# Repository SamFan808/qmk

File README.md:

# qmk
QMK related mechanical keyboard firmware and layouts

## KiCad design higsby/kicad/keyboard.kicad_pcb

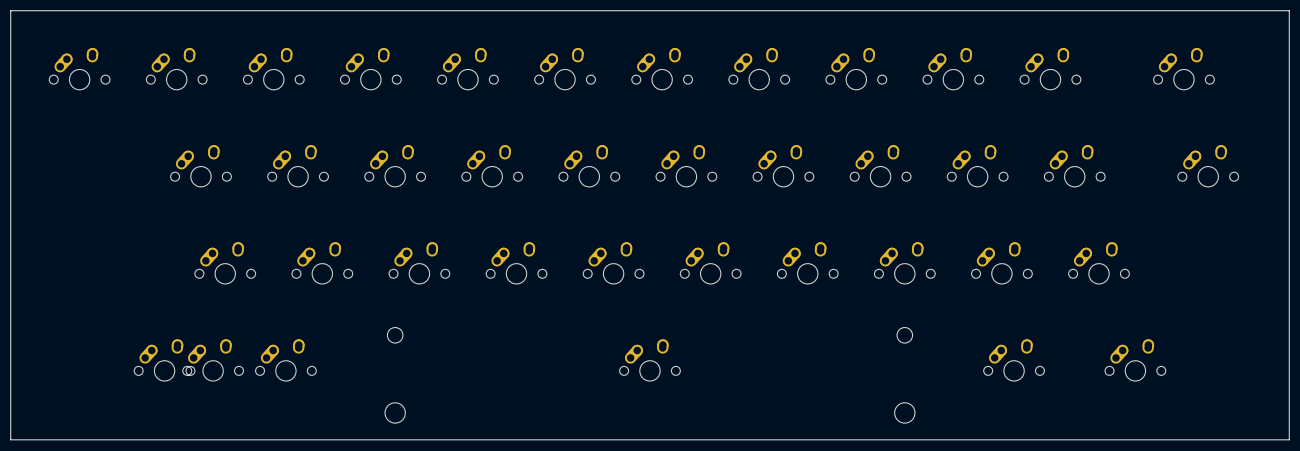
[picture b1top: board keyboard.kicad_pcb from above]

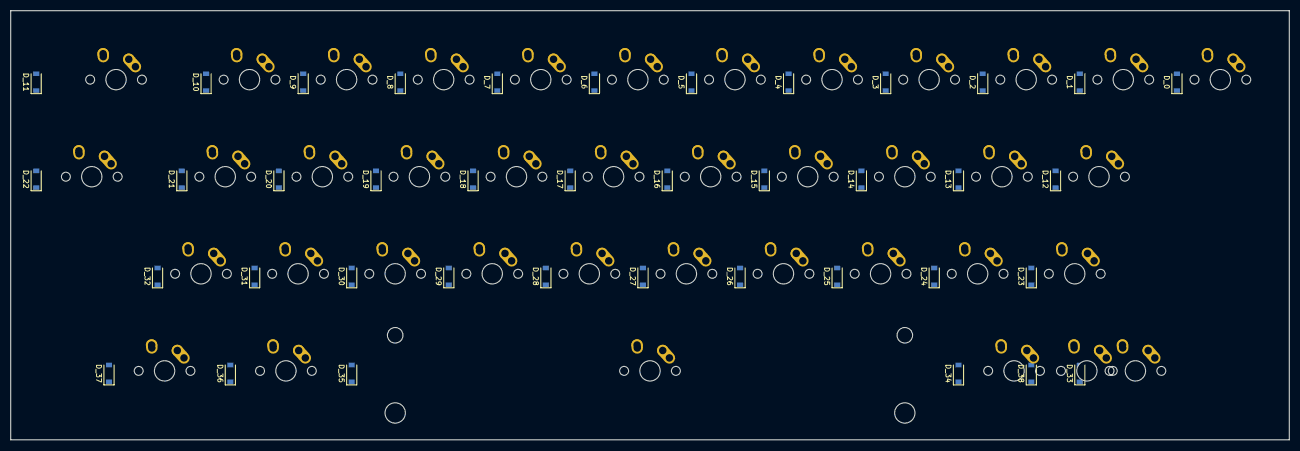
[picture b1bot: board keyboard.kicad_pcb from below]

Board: 2 copper layers, 250.9 x 84.2 mm, 78 parts (39 on the bottom side), 55 nets, no tracks yet.

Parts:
D_0, D_1, D_2, D_3, D_4, D_5, D_6, D_7, D_8, D_9, D_10, D_11, D_12, D_13, D_14, D_15, D_16, D_17, D_18, D_19, D_20, D_21, D_22, D_23, D_24, D_25, D_26, D_27, D_28, D_29, D_30, D_31, D_32, D_33, D_34, D_35, D_36, D_37, D_38: D; D_SOD-123
K_0, K_1, K_2, K_3, K_4, K_5, K_6, K_7, K_8, K_9, K_10, K_12, K_13, K_14, K_15, K_16, K_17, K_18, K_19, K_20, K_21, K_23, K_24, K_25, K_26, K_27, K_28, K_29, K_30, K_31, K_32: KEYSW; MX-1U-NoLED
K_11: KEYSW; MX-1.75U-NoLED
K_22, K_33, K_34, K_36, K_37, K_38: KEYSW; MX-1.25U-NoLED
K_35: KEYSW; MX-6.25U-NoLED

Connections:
unnamed: D_0.2, K_0.2
unnamed: D_1.2, K_1.2
unnamed: D_2.2, K_2.2
unnamed: D_3.2, K_3.2
unnamed: D_4.2, K_4.2
unnamed: D_5.2, K_5.2
unnamed: D_6.2, K_6.2
unnamed: D_7.2, K_7.2
unnamed: D_8.2, K_8.2
unnamed: D_9.2, K_9.2
unnamed: D_10.2, K_10.2
unnamed: D_11.2, K_11.2
unnamed: D_12.2, K_12.2
unnamed: D_13.2, K_13.2
unnamed: D_14.2, K_14.2
unnamed: D_15.2, K_15.2
unnamed: D_16.2, K_16.2
unnamed: D_17.2, K_17.2
unnamed: D_18.2, K_18.2
unnamed: D_19.2, K_19.2
unnamed: D_20.2, K_20.2
unnamed: D_21.2, K_21.2
unnamed: D_22.2, K_22.2
unnamed: D_23.2, K_23.2
unnamed: D_24.2, K_24.2
unnamed: D_25.2, K_25.2
unnamed: D_26.2, K_26.2
unnamed: D_27.2, K_27.2
unnamed: D_28.2, K_28.2
unnamed: D_29.2, K_29.2
unnamed: D_30.2, K_30.2
unnamed: D_31.2, K_31.2
unnamed: D_32.2, K_32.2
unnamed: D_33.2, K_33.2
unnamed: D_34.2, K_34.2
unnamed: D_35.2, K_35.2
unnamed: D_36.2, K_36.2
unnamed: D_37.2, K_37.2
unnamed: D_38.2, K_38.2
col0: K_0.1, K_38.1
col1: K_1.1, K_12.1, K_33.1
col2: K_2.1, K_13.1, K_23.1, K_34.1
col3: K_3.1, K_14.1, K_24.1
col4: K_4.1, K_15.1, K_25.1
col5: K_5.1, K_16.1, K_26.1
col6: K_6.1, K_17.1, K_27.1, K_35.1
col7: K_7.1, K_18.1, K_28.1
col8: K_8.1, K_19.1, K_29.1
col9: K_9.1, K_20.1, K_30.1
col10: K_10.1, K_21.1, K_31.1, K_36.1
col11: K_11.1, K_32.1, K_37.1
row0: D_0.1, D_1.1, D_2.1, D_3.1, D_4.1, D_5.1, D_6.1, D_7.1, D_8.1, D_9.1, D_10.1, D_11.1
row1: D_12.1, D_13.1, D_14.1, D_15.1, D_16.1, D_17.1, D_18.1, D_19.1, D_20.1, D_21.1
row2: D_22.1, D_23.1, D_24.1, D_25.1, D_26.1, D_27.1, D_28.1, D_29.1, D_30.1, D_31.1, D_32.1, D_38.1
row3: D_33.1, D_34.1, D_35.1, D_36.1, D_37.1

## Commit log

2020-09-30 updating files and directory
2020-12-06 added working qaz layout
2020-12-07 additional key layouts added
2020-12-09 updated qaz.json
2020-12-14 updated reviung map, prime-e
2021-01-01 tweaked QAZ and a few other keymaps
2021-01-23 updating and adding keymaps and firmware builds for new keebs
2021-01-25 revised QAZ, _33 and a few others
2021-02-11 updated ut47 map
2021-02-20 added ISOgamer
2021-03-05 added isgamer
2021-04-01 modified ISO Gamer layout and firmware, added some plate files
2021-04-03 added updated isogamer firmware
2021-04-09 updated ut47.2 layout
2021-04-15 added ketch, and updated underscore33 maps
2021-06-15 updating a number of files
2021-07-19 updating keeb maps
2021-08-22 updating hex files for yasui
2021-08-24 adjusting ble-chiffre keymap
2021-08-30 added ketch vial fiiles, mockup images
2021-09-03 modified ble_chiffre keymap
2021-09-07 updating ble-chiffre map
2021-09-10 updated ble-chiffre
2021-09-17 updated leftover map
2021-09-25 revised underscore33 map
2021-10-17 updated prime_e pants
2021-10-24 updating nomu30 and leftover30_arm
2021-10-24 updating leftover30_arm volume encoder
2021-10-26 updated leftover30 layout
2021-11-03 added treadstone32_c firmware
2021-11-06 updating dimple
2021-11-12 adding dimple firmwares
2021-11-14 added minisub vial
2021-11-18 updating file structure
2021-12-16 updated underscore33 keymap
2021-12-16 updating underscore33 keymap
2021-12-23 updating files, adalyn
2022-01-21 updated qaz vial
2022-01-23 updated isogamer
2022-02-15 updating planck keymap
2022-04-05 added v4n4g0n firmware
2022-05-11 updating minisub and v4n4g0n
2022-06-28 updating mock ups and several firmwares
2022-06-29 added taco truck plates
2023-05-28 many updates
